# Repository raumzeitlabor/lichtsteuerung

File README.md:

RaumZeitLabor Lichtsteuerung
============================

https://wiki.raumzeitlabor.de/wiki/Lichtsteuerung

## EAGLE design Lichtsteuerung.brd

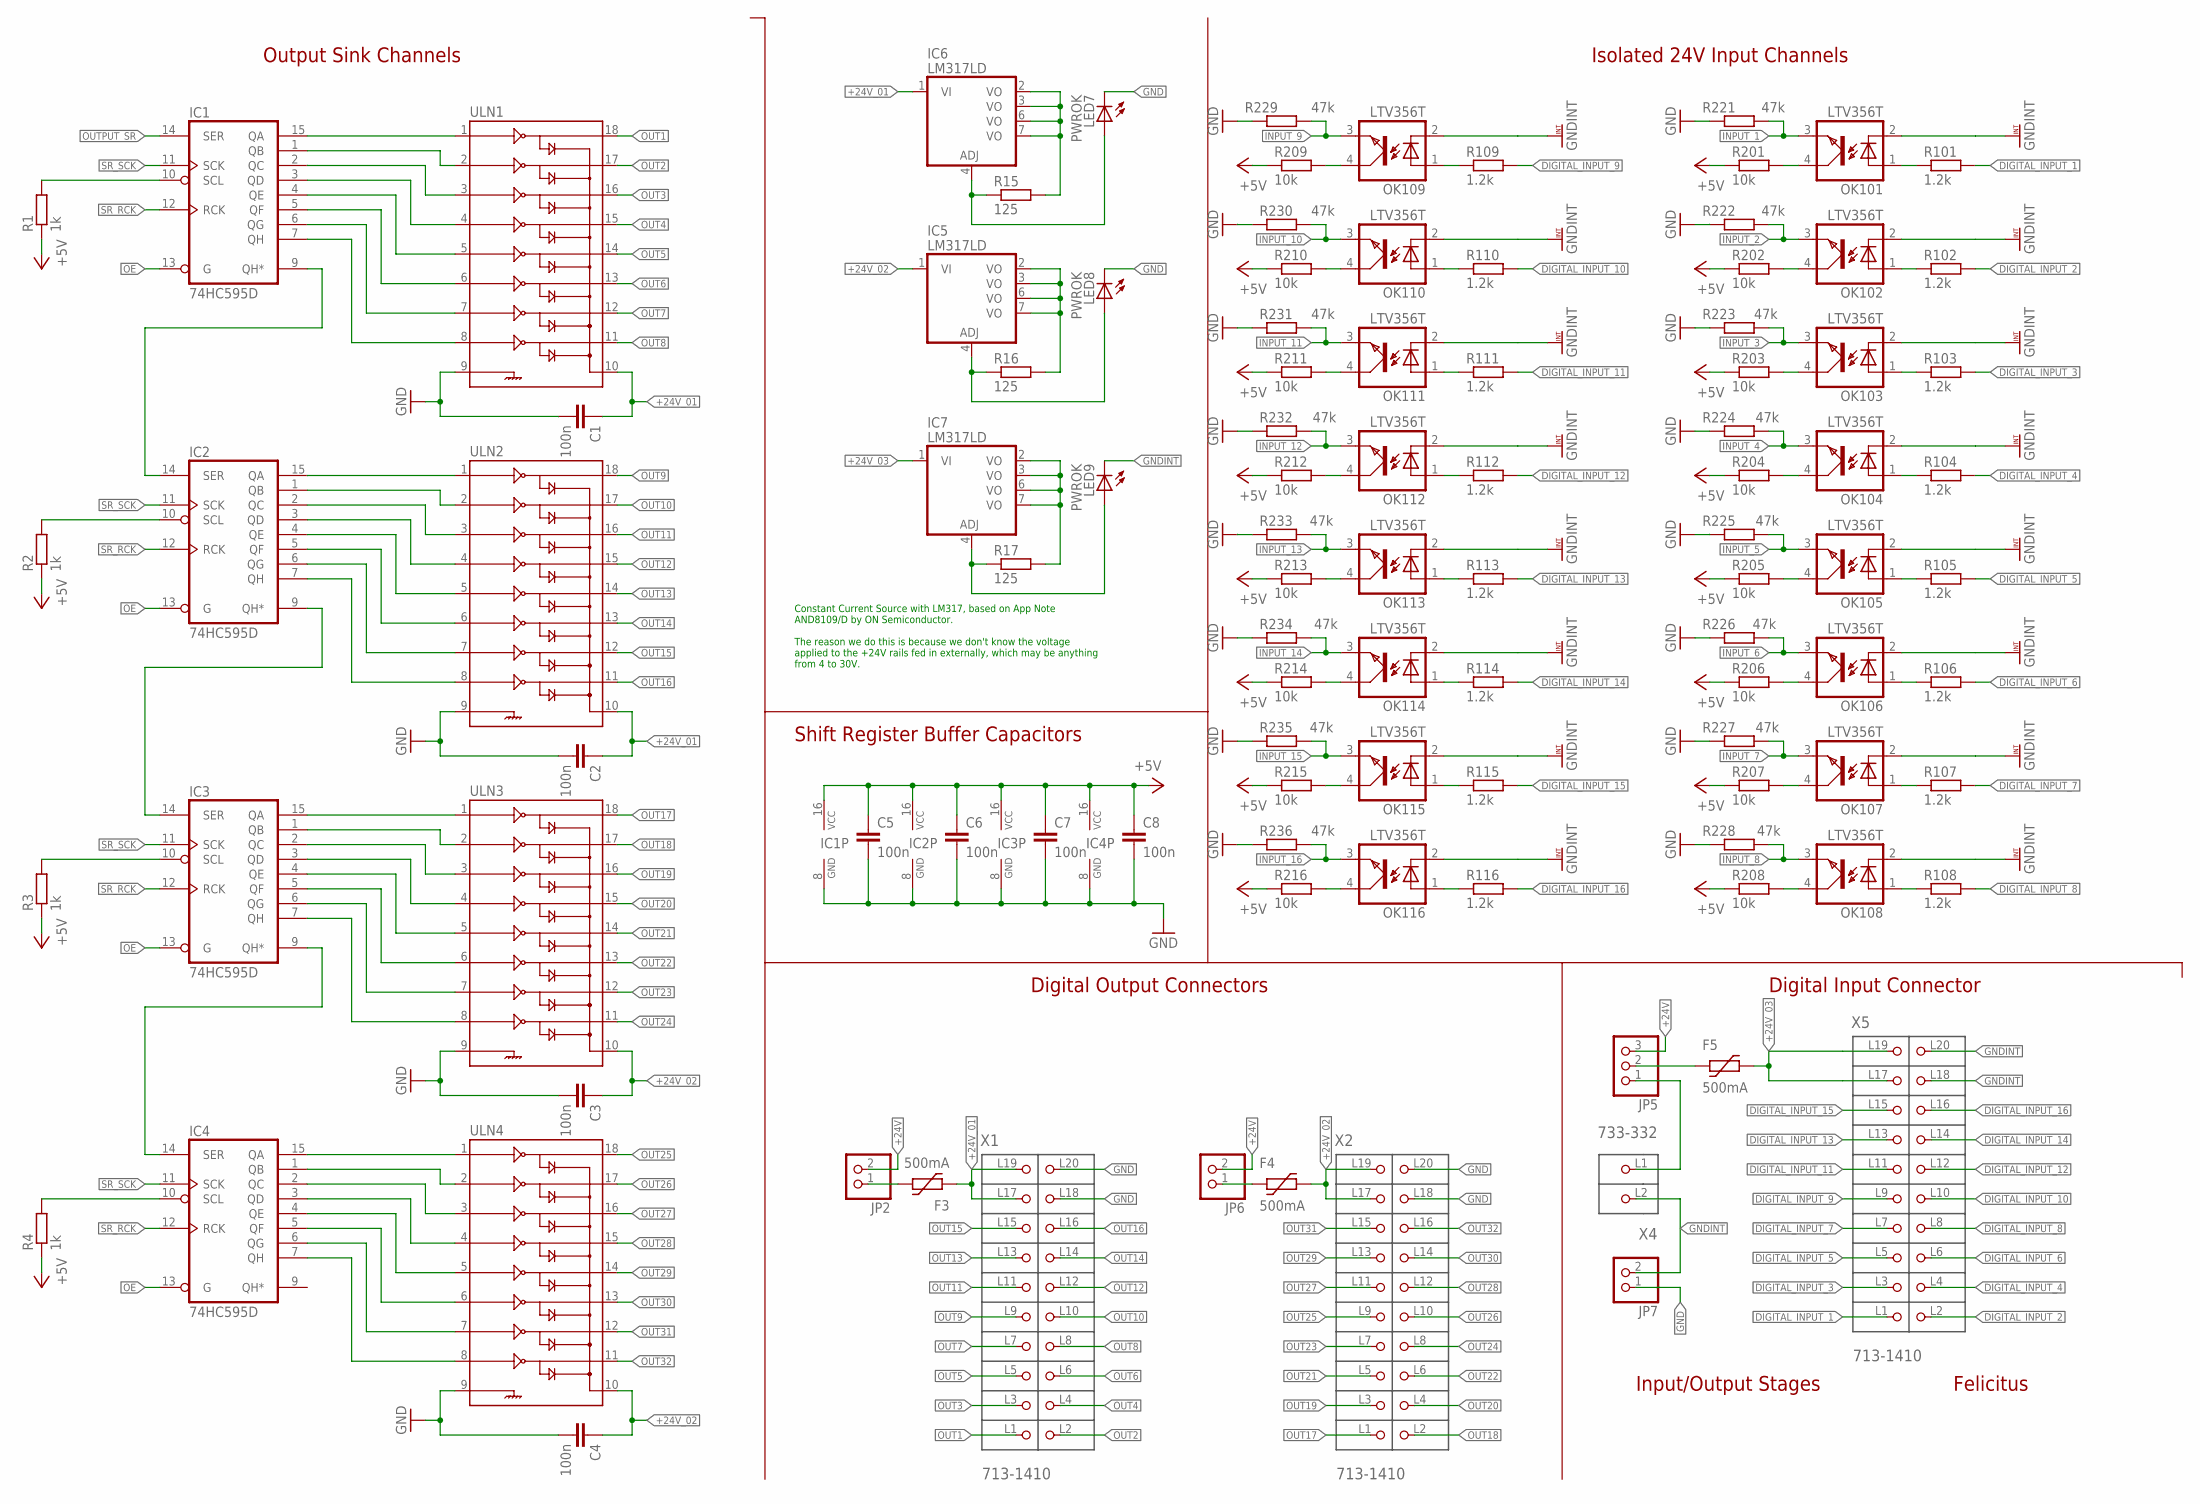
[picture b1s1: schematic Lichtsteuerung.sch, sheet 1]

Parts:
C1, C2, C3, C4, C5, C6, C7, C8: 100n; C0805
F3, F4, F5: 500mA; 1812L
IC1, IC2, IC3, IC4: 74HC595D; SO16
IC5, IC6, IC7: LM317LD; SO08
JP2, JP6, JP7: PINHD-1X2; 1X02
JP5: PINHD-1X3; 1X03
LED7, LED8, LED9: PWROK; CHIP-LED0805
OK101, OK102, OK103, OK104, OK105, OK106, OK107, OK108, OK109, OK110, OK111, OK112, OK113, OK114, OK115, OK116: LTV356T; SMD4
R1, R2, R3, R4: 1k; R0805
R15, R16, R17: 125; R0805
R101, R102, R103, R104, R105, R106, R107, R108, R109, R110, R111, R112, R113, R114, R115, R116: 1.2k; R0805
R201, R202, R203, R204, R205, R206, R207, R208, R209, R210, R211, R212, R213, R214, R215, R216: 10k; R0805
R221, R222, R223, R224, R225, R226, R227, R228, R229, R230, R231, R232, R233, R234, R235, R236: 47k; R0805
ULN1, ULN2, ULN3, ULN4: ULN2803SOICW; SO18L
X1, X2, X5: 713-1410; P-713-1410
X4: 733-332; P-733-332

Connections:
+5V: C5.1, C6.1, C7.1, C8.1, IC1.16 (VCC), IC2.16 (VCC), IC3.16 (VCC), IC4.16 (VCC), R1.1, R2.1, R3.1, R4.1, R201.1, R202.1, R203.1, R204.1, R205.1, R206.1, R207.1, R208.1, R209.1, R210.1, R211.1, R212.1, R213.1, R214.1, R215.1, R216.1; also elsewhere on the board
+24V: JP2.2, JP5.3, JP6.2; also elsewhere on the board
+24V_01: C1.1, C2.1, F3.P$1 (1), IC6.1 (VI), ULN1.10, ULN2.10, X1.L17, X1.L19
+24V_02: C3.1, C4.1, F4.P$2 (2), IC5.1 (VI), ULN3.10, ULN4.10, X2.L17, X2.L19
+24V_03: F5.P$2 (2), IC7.1 (VI), X5.L17, X5.L19
DIGITAL_INPUT_1: R101.2, X5.L1
DIGITAL_INPUT_2: R102.2, X5.L2
DIGITAL_INPUT_3: R103.2, X5.L3
DIGITAL_INPUT_4: R104.2, X5.L4
DIGITAL_INPUT_5: R105.2, X5.L5
DIGITAL_INPUT_6: R106.2, X5.L6
DIGITAL_INPUT_7: R107.2, X5.L7
DIGITAL_INPUT_8: R108.2, X5.L8
DIGITAL_INPUT_9: R109.2, X5.L9
DIGITAL_INPUT_10: R110.2, X5.L10
DIGITAL_INPUT_11: R111.2, X5.L11
DIGITAL_INPUT_12: R112.2, X5.L12
DIGITAL_INPUT_13: R113.2, X5.L13
DIGITAL_INPUT_14: R114.2, X5.L14
DIGITAL_INPUT_15: R115.2, X5.L15
DIGITAL_INPUT_16: R116.2, X5.L16
GND: C1.2, C2.2, C3.2, C4.2, C5.2, C6.2, C7.2, C8.2, IC1.8 (GND), IC2.8 (GND), IC3.8 (GND), IC4.8 (GND), JP7.1, LED7.C, LED8.C, R221.1, R222.1, R223.1, R224.1, R225.1, R226.1, R227.1, R228.1, R229.1, R230.1, R231.1, R232.1, R233.1, R234.1, R235.1, R236.1, ULN1.9, ULN2.9, ULN3.9, ULN4.9, X1.L18, X1.L20, X2.L18, X2.L20; also elsewhere on the board
GNDINT: JP7.2, LED9.C, OK101.2 (C), OK102.2 (C), OK103.2 (C), OK104.2 (C), OK105.2 (C), OK106.2 (C), OK107.2 (C), OK108.2 (C), OK109.2 (C), OK110.2 (C), OK111.2 (C), OK112.2 (C), OK113.2 (C), OK114.2 (C), OK115.2 (C), OK116.2 (C), X4.L2 (P2), X5.L18, X5.L20; also elsewhere on the board
INPUT_1: OK101.3 (EMIT), R221.2; also elsewhere on the board
INPUT_2: OK102.3 (EMIT), R222.2; also elsewhere on the board
INPUT_3: OK103.3 (EMIT), R223.2; also elsewhere on the board
INPUT_4: OK104.3 (EMIT), R224.2; also elsewhere on the board
INPUT_5: OK105.3 (EMIT), R225.2; also elsewhere on the board
INPUT_6: OK106.3 (EMIT), R226.2; also elsewhere on the board
INPUT_7: OK107.3 (EMIT), R227.2; also elsewhere on the board
INPUT_8: OK108.3 (EMIT), R228.2; also elsewhere on the board
INPUT_9: OK109.3 (EMIT), R229.2; also elsewhere on the board
INPUT_10: OK110.3 (EMIT), R230.2; also elsewhere on the board
INPUT_11: OK111.3 (EMIT), R231.2; also elsewhere on the board
INPUT_12: OK112.3 (EMIT), R232.2; also elsewhere on the board
INPUT_13: OK113.3 (EMIT), R233.2; also elsewhere on the board
INPUT_14: OK114.3 (EMIT), R234.2; also elsewhere on the board
INPUT_15: OK115.3 (EMIT), R235.2; also elsewhere on the board
INPUT_16: OK116.3 (EMIT), R236.2; also elsewhere on the board
unnamed: IC1.15 (QA), ULN1.1
unnamed: IC1.1 (QB), ULN1.2
unnamed: IC1.2 (QC), ULN1.3
unnamed: IC1.3 (QD), ULN1.4
unnamed: IC1.4 (QE), ULN1.5
unnamed: IC1.5 (QF), ULN1.6
unnamed: IC1.6 (QG), ULN1.7
unnamed: IC1.7 (QH), ULN1.8
unnamed: IC2.15 (QA), ULN2.1
unnamed: IC2.1 (QB), ULN2.2
unnamed: IC2.2 (QC), ULN2.3
unnamed: IC2.3 (QD), ULN2.4
unnamed: IC2.4 (QE), ULN2.5
unnamed: IC2.5 (QF), ULN2.6
unnamed: IC2.6 (QG), ULN2.7
unnamed: IC2.7 (QH), ULN2.8
unnamed: IC3.15 (QA), ULN3.1
unnamed: IC3.1 (QB), ULN3.2
unnamed: IC3.2 (QC), ULN3.3
unnamed: IC3.3 (QD), ULN3.4
unnamed: IC3.4 (QE), ULN3.5
unnamed: IC3.5 (QF), ULN3.6
unnamed: IC3.6 (QG), ULN3.7
unnamed: IC3.7 (QH), ULN3.8
unnamed: IC4.15 (QA), ULN4.1
unnamed: IC4.1 (QB), ULN4.2
unnamed: IC4.2 (QC), ULN4.3
unnamed: IC4.3 (QD), ULN4.4
unnamed: IC4.4 (QE), ULN4.5
unnamed: IC4.5 (QF), ULN4.6
unnamed: IC4.6 (QG), ULN4.7
unnamed: IC4.7 (QH), ULN4.8
unnamed: IC1.9 (QH*), IC2.14 (SER)
unnamed: IC2.9 (QH*), IC3.14 (SER)
unnamed: IC3.9 (QH*), IC4.14 (SER)
unnamed: IC1.10 (SCL), R1.2
unnamed: IC2.10 (SCL), R2.2
unnamed: IC3.10 (SCL), R3.2
unnamed: IC4.10 (SCL), R4.2
unnamed: F5.P$1 (1), JP5.2
unnamed: JP5.1, X4.L1 (P1)
unnamed: OK101.1 (A), R101.1
unnamed: OK101.4 (COL), R201.2
unnamed: OK102.1 (A), R102.1
unnamed: OK102.4 (COL), R202.2
unnamed: OK103.1 (A), R103.1
unnamed: OK103.4 (COL), R203.2
unnamed: OK104.1 (A), R104.1
unnamed: OK104.4 (COL), R204.2
unnamed: OK105.1 (A), R105.1
unnamed: OK105.4 (COL), R205.2
unnamed: OK106.1 (A), R106.1
unnamed: OK106.4 (COL), R206.2
unnamed: OK107.1 (A), R107.1
unnamed: OK107.4 (COL), R207.2
unnamed: OK108.1 (A), R108.1
unnamed: OK108.4 (COL), R208.2
unnamed: OK109.1 (A), R109.1
unnamed: OK109.4 (COL), R209.2
unnamed: OK110.1 (A), R110.1
unnamed: OK110.4 (COL), R210.2
unnamed: OK111.1 (A), R111.1
unnamed: F4.P$1 (1), JP6.1
unnamed: OK111.4 (COL), R211.2
unnamed: F3.P$2 (2), JP2.1
unnamed: OK112.1 (A), R112.1
unnamed: IC5.4 (ADJ), LED8.A, R16.1
unnamed: OK112.4 (COL), R212.2
unnamed: IC5.2 (VO), IC5.3 (VO), IC5.6 (VO), IC5.7 (VO), R16.2
unnamed: IC7.4 (ADJ), LED9.A, R17.1
unnamed: OK113.1 (A), R113.1
unnamed: IC6.4 (ADJ), LED7.A, R15.1
unnamed: IC6.2 (VO), IC6.3 (VO), IC6.6 (VO), IC6.7 (VO), R15.2
unnamed: OK113.4 (COL), R213.2
unnamed: IC7.2 (VO), IC7.3 (VO), IC7.6 (VO), IC7.7 (VO), R17.2
unnamed: OK114.1 (A), R114.1
unnamed: OK114.4 (COL), R214.2
unnamed: OK115.1 (A), R115.1
unnamed: OK115.4 (COL), R215.2
unnamed: OK116.1 (A), R116.1
unnamed: OK116.4 (COL), R216.2
OE: IC1.13 (G), IC2.13 (G), IC3.13 (G), IC4.13 (G); also elsewhere on the board
OUT1: ULN1.18, X1.L1
OUT2: ULN1.17, X1.L2
OUT3: ULN1.16, X1.L3
OUT4: ULN1.15, X1.L4
OUT5: ULN1.14, X1.L5
OUT6: ULN1.13, X1.L6
OUT7: ULN1.12, X1.L7
OUT8: ULN1.11, X1.L8
OUT9: ULN2.18, X1.L9
OUT10: ULN2.17, X1.L10
OUT11: ULN2.16, X1.L11
OUT12: ULN2.15, X1.L12
OUT13: ULN2.14, X1.L13
OUT14: ULN2.13, X1.L14
OUT15: ULN2.12, X1.L15
OUT16: ULN2.11, X1.L16
OUT17: ULN3.18, X2.L1
OUT18: ULN3.17, X2.L2
OUT19: ULN3.16, X2.L3
OUT20: ULN3.15, X2.L4
OUT21: ULN3.14, X2.L5
OUT22: ULN3.13, X2.L6
OUT23: ULN3.12, X2.L7
OUT24: ULN3.11, X2.L8
OUT25: ULN4.18, X2.L9
OUT26: ULN4.17, X2.L10
OUT27: ULN4.16, X2.L11
OUT28: ULN4.15, X2.L12
OUT29: ULN4.14, X2.L13
OUT30: ULN4.13, X2.L14
OUT31: ULN4.12, X2.L15
OUT32: ULN4.11, X2.L16
OUTPUT_SR: IC1.14 (SER); also elsewhere on the board
SR_RCK: IC1.12 (RCK), IC2.12 (RCK), IC3.12 (RCK), IC4.12 (RCK); also elsewhere on the board
SR_SCK: IC1.11 (SCK), IC2.11 (SCK), IC3.11 (SCK), IC4.11 (SCK); also elsewhere on the board

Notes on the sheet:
Felicitus
Output Sink Channels
Shift Register Buffer Capacitors
Input/Output Stages
Isolated 24V Input Channels
Digital Input Connector
Digital Output Connectors
Constant Current Source with LM317, based on App Note AND8109/D by ON Semiconductor. The reason we do this is because we don't know the voltage applied to the +24V rails fed in externally, which may be anything from 4 to 30V.

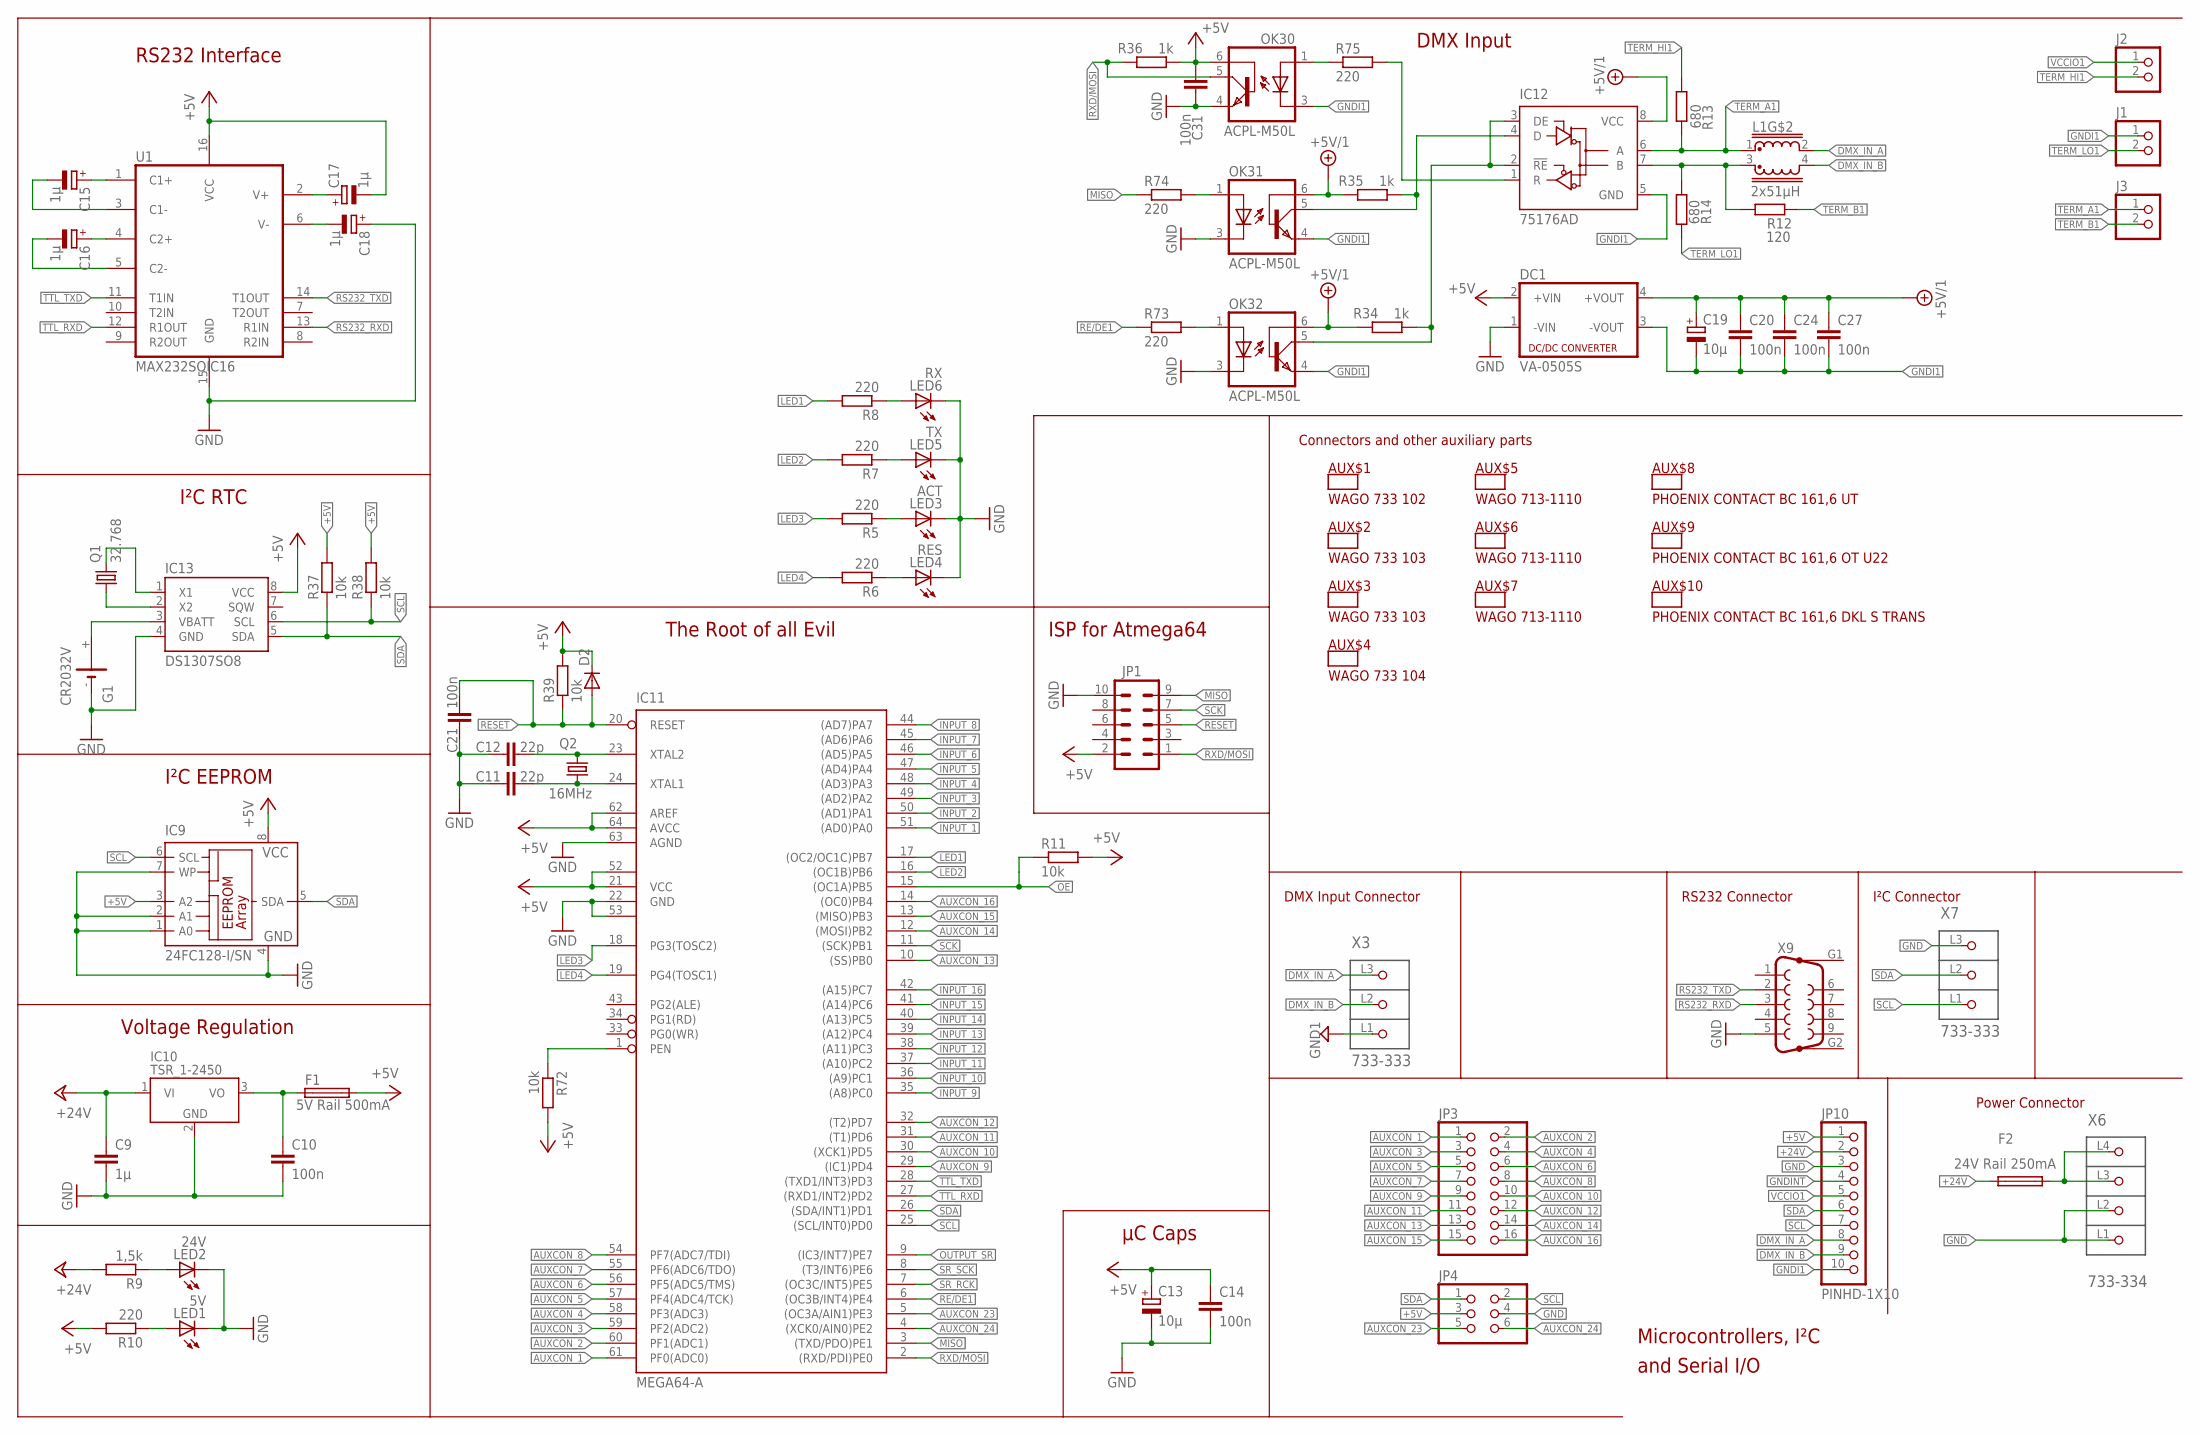
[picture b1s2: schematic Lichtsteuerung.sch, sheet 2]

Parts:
C9: 1µ; C0805
C10, C14, C20, C21, C24, C27, C31: 100n; C0805
C11, C12: 22p; C0805
C13, C19: 10µ; C/6032-28R; PARTKEEPR_SKU 2607
C15, C16, C17, C18: 1µ; A/3216-18R; PARTKEEPR_SKU 2609
D2: DIODE-SOD323-R; SOD323-R
DC1: VA-0505S; 4SIL
F1: 5V Rail 500mA; OMNIBLOK
F2: 24V Rail 250mA; OMNIBLOK
G1: CR2032V; CR2032V2
IC9: 24FC128-I/SN; SO-08M
IC10: TSR_1-2450; TSR-1
IC11: MEGA64-A; TQFP64
IC12: 75176AD; D_R-PDSO-G8
IC13: DS1307SO8; SO08
J1, J2, J3: PINHD-1X2; 1X02
JP1: ML10
JP3: PINHD-2X8; 2X08
JP4: PINHD-2X3; 2X03
JP10: PINHD-1X10; 1X10-BIG
L1: 2x51µH; EPCOS_B82790_SERIES
LED1: 5V; CHIP-LED0805
LED2: 24V; CHIP-LED0805
LED3: ACT; CHIP-LED0805
LED4: RES; CHIP-LED0805
LED5: TX; CHIP-LED0805
LED6: RX; CHIP-LED0805
OK30, OK31, OK32: ACPL-M50L; JEDEC_MS-012-AA_SOIC5
Q1: 32.768; MC-306
Q2: 16MHz; MJ
R5, R6, R7, R8, R10, R73, R74, R75: 220; R0805
R9: 1,5k; R0805
R11, R37, R38, R39, R72: 10k; R0805
R12: 120; R0805
R13, R14: 680; R0805
R34, R35, R36: 1k; R0805
U1: MAX232SOIC16; SO016
X3, X7: 733-333; P-733-333
X6: 733-334; P-733-334
X9: F09VP

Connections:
+5V: C13.+, C14.1, C17.-, C31.1, D2.C, DC1.2 (+VIN), F1.P$2 (2), IC9.3 (A2), IC9.8 (VCC), IC11.21 (VCC), IC11.52 (VCC1), IC11.62 (AREF), IC11.64 (AVCC), IC13.8 (VCC), JP1.2, JP4.3, JP10.1, OK30.6 (BAS), R10.2, R11.2, R36.1, R37.2, R38.2, R39.2, R72.2, U1.16 (VCC); also elsewhere on the board
+24V: C9.1, F2.P$1 (1), IC10.1 (VI), JP10.2, R9.2; also elsewhere on the board
+24VIN: F2.P$2 (2), X6.L3 (P3), X6.L4 (P4)
AUXCON_1: IC11.61 (PF0(ADC0)), JP3.1
AUXCON_2: IC11.60 (PF1(ADC1)), JP3.2
AUXCON_3: IC11.59 (PF2(ADC2)), JP3.3
AUXCON_4: IC11.58 (PF3(ADC3)), JP3.4
AUXCON_5: IC11.57 (PF4(ADC4/TCK)), JP3.5
AUXCON_6: IC11.56 (PF5(ADC5/TMS)), JP3.6
AUXCON_7: IC11.55 (PF6(ADC6/TDO)), JP3.7
AUXCON_8: IC11.54 (PF7(ADC7/TDI)), JP3.8
AUXCON_9: IC11.29 ((IC1)PD4), JP3.9
AUXCON_10: IC11.30 ((XCK1)PD5), JP3.10
AUXCON_11: IC11.31 ((T1)PD6), JP3.11
AUXCON_12: IC11.32 ((T2)PD7), JP3.12
AUXCON_13: IC11.10 ((SS)PB0), JP3.13
AUXCON_14: IC11.12 ((MOSI)PB2), JP3.14
AUXCON_15: IC11.13 ((MISO)PB3), JP3.15
AUXCON_16: IC11.14 ((OC0)PB4), JP3.16
AUXCON_23: IC11.5 ((OC3A/AIN1)PE3), JP4.5
AUXCON_24: IC11.4 ((XCK0/AIN0)PE2), JP4.6
DMX_IN_A: JP10.8, L1.2 (4), X3.L3 (P3)
DMX_IN_B: JP10.9, L1.4, X3.L2 (P2)
GND: C9.2, C10.2, C11.2, C12.2, C13.-, C14.2, C18.+, C21.2, C31.2, DC1.1 (-VIN), G1.-, IC9.1 (A0), IC9.2 (A1), IC9.4 (GND), IC9.7 (WP), IC10.2 (GND), IC11.22 (GND), IC11.53 (GND1), IC11.63 (AGND), IC13.4 (GND), JP1.10, JP4.4, JP10.3, LED1.C, LED2.C, LED3.C, LED4.C, LED5.C, LED6.C, OK30.4 (EMI), OK31.3 (C), OK32.3 (C), U1.15 (GND), X6.L1 (P1), X6.L2 (P2), X7.L3 (P3), X9.5; also elsewhere on the board
GNDI1: C19.-, C20.2, C24.2, C27.2, DC1.3 (-VOUT), IC12.5 (GND), J1.1, JP10.10, OK30.3 (C), OK31.4 (EMI), OK32.4 (EMI), X3.L1 (P1)
GNDINT: JP10.4; also elsewhere on the board
INPUT_1: IC11.51 ((AD0)PA0); also elsewhere on the board
INPUT_2: IC11.50 ((AD1)PA1); also elsewhere on the board
INPUT_3: IC11.49 ((AD2)PA2); also elsewhere on the board
INPUT_4: IC11.48 ((AD3)PA3); also elsewhere on the board
INPUT_5: IC11.47 ((AD4)PA4); also elsewhere on the board
INPUT_6: IC11.46 ((AD5)PA5); also elsewhere on the board
INPUT_7: IC11.45 ((AD6)PA6); also elsewhere on the board
INPUT_8: IC11.44 ((AD7)PA7); also elsewhere on the board
INPUT_9: IC11.35 ((A8)PC0); also elsewhere on the board
INPUT_10: IC11.36 ((A9)PC1); also elsewhere on the board
INPUT_11: IC11.37 ((A10)PC2); also elsewhere on the board
INPUT_12: IC11.38 ((A11)PC3); also elsewhere on the board
INPUT_13: IC11.39 ((A12)PC4); also elsewhere on the board
INPUT_14: IC11.40 ((A13)PC5); also elsewhere on the board
INPUT_15: IC11.41 ((A14)PC6); also elsewhere on the board
INPUT_16: IC11.42 ((A15)PC7); also elsewhere on the board
LED1: IC11.17 ((OC2/OC1C)PB7), R8.2
LED2: IC11.16 ((OC1B)PB6), R7.2
LED3: IC11.18 (PG3(TOSC2)), R5.2
LED4: IC11.19 (PG4(TOSC1)), R6.2
MISO: IC11.3 ((TXD/PDO)PE1), JP1.9, R74.1
unnamed: G1.+, IC13.3 (VBATT)
unnamed: C11.1, IC11.24 (XTAL1), Q2.P3 (2)
unnamed: IC13.2 (X2), Q1.1
unnamed: IC13.1 (X1), Q1.4 (2)
unnamed: C12.1, IC11.23 (XTAL2), Q2.P1 (1)
unnamed: LED6.A, R8.1
unnamed: LED5.A, R7.1
unnamed: LED3.A, R5.1
unnamed: C15.+, U1.1 (C1+)
unnamed: C15.-, U1.3 (C1-)
unnamed: LED4.A, R6.1
unnamed: LED1.A, R10.1
unnamed: LED2.A, R9.1
unnamed: IC11.1 (PEN), R72.1
unnamed: C16.+, U1.4 (C2+)
unnamed: C16.-, U1.5 (C2-)
unnamed: C10.1, F1.P$1 (1), IC10.3 (VO)
unnamed: IC12.7 (B), L1.3 (1), R12.2, R14.2
unnamed: OK30.1 (A), R75.1
unnamed: OK31.1 (A), R74.2
unnamed: OK32.1 (A), R73.2
unnamed: C18.-, U1.6 (V-)
unnamed: C17.+, U1.2 (V+)
OE: IC11.15 ((OC1A)PB5), R11.1; also elsewhere on the board
OUTPUT_SR: IC11.9 ((IC3/INT7)PE7); also elsewhere on the board
RE/DE1: IC11.6 ((OC3B/INT4)PE4), R73.1
REC$1: IC12.1 (R), R75.2
RESET: C21.1, D2.A, IC11.20 (RESET), JP1.5, R39.1
RE_OUT: IC12.2 (!RE), IC12.3 (DE), OK32.5 (COL), R34.1
RS232_RXD: U1.13 (R1IN), X9.3
RS232_TXD: U1.14 (T1OUT), X9.2
RXD/MOSI: IC11.2 ((RXD/PDI)PE0), JP1.1, OK30.5 (COL), R36.2
SCK: IC11.11 ((SCK)PB1), JP1.7
SCL: IC9.6 (SCL), IC11.25 ((SCL/INT0)PD0), IC13.6 (SCL), JP4.2, JP10.7, R38.1, X7.L1 (P1)
SDA: IC9.5 (SDA), IC11.26 ((SDA/INT1)PD1), IC13.5 (SDA), JP4.1, JP10.6, R37.1, X7.L2 (P2)
SR_RCK: IC11.7 ((OC3C/INT5)PE5); also elsewhere on the board
SR_SCK: IC11.8 ((T3/INT6)PE6); also elsewhere on the board
TERM_A1: IC12.6 (A), J3.1, L1.1, R13.1
TERM_B1: J3.2, R12.1
TERM_HI1: J2.2, R13.2
TERM_LO1: J1.2, R14.1
TTL_RXD: IC11.27 ((RXD1/INT2)PD2), U1.12 (R1OUT)
TTL_TXD: IC11.28 ((TXD1/INT3)PD3), U1.11 (T1IN)
TXD_OUT: IC12.4 (D), OK31.5 (COL), R35.1
VCCIO1: C19.+, C20.1, C24.1, C27.1, DC1.4 (+VOUT), IC12.8 (VCC), J2.1, JP10.5, OK31.6 (BAS), OK32.6 (BAS), R34.2, R35.2

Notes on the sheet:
I²C EEPROM
I²C RTC
Voltage Regulation
DMX Input
ISP for Atmega64
µC Caps
RS232 Interface
The Root of all Evil
Microcontrollers, I²C
and Serial I/O
DMX Input Connector
RS232 Connector
I²C Connector
Power Connector
Connectors and other auxiliary parts

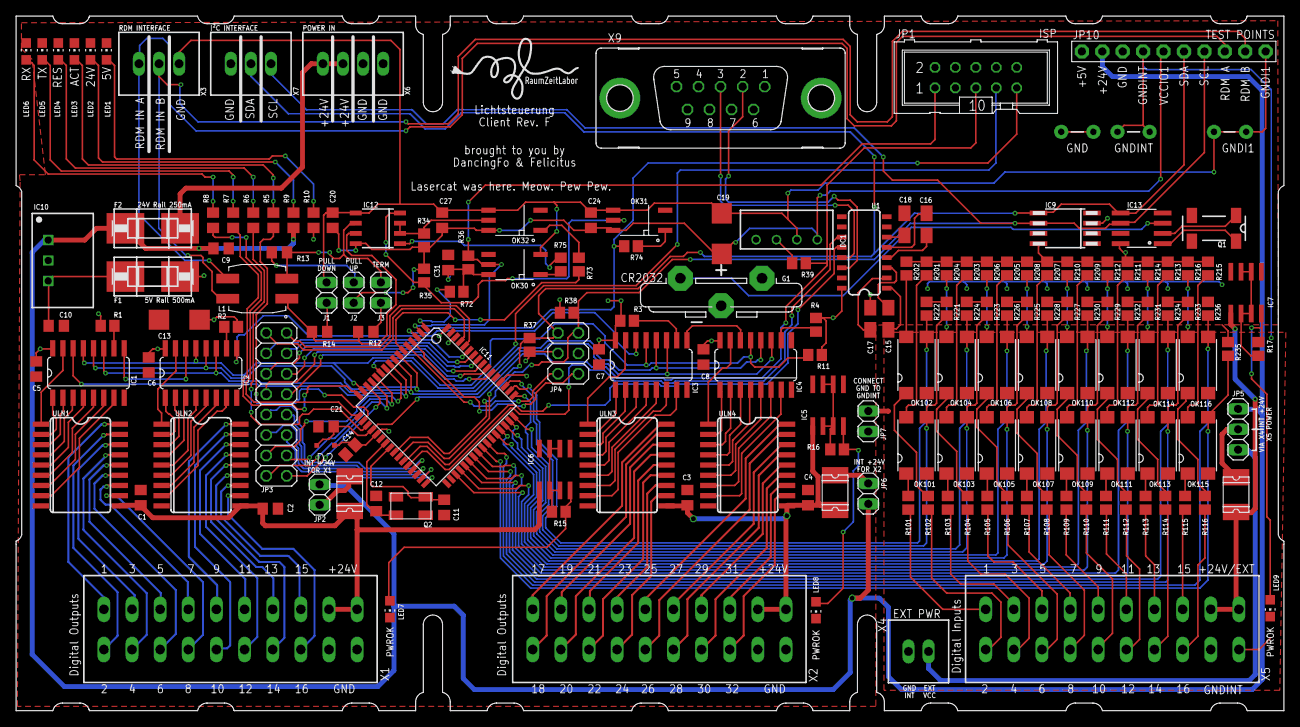
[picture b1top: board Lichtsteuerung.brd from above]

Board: 2 copper layers, 157.7 x 86.4 mm, 175 parts (0 on the bottom side), 224 nets.

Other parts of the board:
U$1: RAUMZEITLABOR_FILLED_16MM

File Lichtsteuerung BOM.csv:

Qty	Value	Device	Package	Parts	Description	MF	MPN	OC_FARNELL	OC_NEWARK	OC_REICHELT	EP	GP
1		F09VP	F09VP	X9	SUB-D			unknown	unknown	D-SUB BU 09TL	1,95	1,95
1		PINHD-2X8	2X08	JP3	PIN HEADER					SL 2X10G 2,54	0,07	0,07
4		ULN2803SOICW	SO18L	ULN1, ULN2, ULN3, ULN4	Darlington Driver					ULN 2803 D	0,42	1,68
16	1.2k	R-EU_R0805	R0805	R101, R102, R103, R104, R105, R106, R107, R108, R109, R110, R111, R112, R113, R114, R115, R116	RESISTOR, European symbol					SMD-0805 1,20K	0,025	0,4
3	100n	C-EUC0805	C0805	C10, C20, C23	CAPACITOR, European symbol					X7R-G0805 100N	0,05	0,15
8	100n	C-EUC0805	C0805	C1, C2, C3, C4, C5, C6, C7, C8	CAPACITOR, European symbol					X7R-G0805 100N	0,05	0,4
1	100n	C-EUC0805	C0805@1	C14	CAPACITOR, European symbol					X7R-G0805 100N	0,05	0,05
23	10k	R-EU_R0805	R0805	R8, R37, R38, R39, R40, R72, R76, R201, R202, R203, R204, R205, R206, R207, R208, R209, R210, R211, R212, R213, R214, R215, R216	RESISTOR, European symbol					SMD-0805 10,0K	0,025	0,575
1	125mA	SMD-MICRO-FUSE-BLOCK	OMNIBLOK	F2						SMD-HASF 0,25A	1,1	1,1
2	16MHz	CRYSTALCTS406	CTS406	Q2, Q3	CRYSTAL			unknown	unknown	16,000000-MQ	0,75	1,5
4	1k	R-EU_R0805	R0805	R1, R2, R3, R4	RESISTOR, European symbol					SMD-0805 1,00K	0,025	0,1
4	1µ	CPOL-EU153CLV-0405	153CLV-0405	C15, C16, C17, C18	POLARIZED CAPACITOR, European symbol					VF 1,0/50 C-B	0,15	0,6
6	220	R-EU_R0805	R0805	R5, R6, R7, R73, R74, R75	RESISTOR, European symbol					SMD-0805 220	0,025	0,15
1	220µ	CPOL-EU150CLZ-1010	150CLZ-1010	C13	POLARIZED CAPACITOR, European symbol					VF 220/6,3 K-D	0,14	0,14
2	220µ	CPOL-EUD	PANASONIC_D	C19, C22	POLARIZED CAPACITOR, European symbol					VF 220/6,3 K-D	0,14	0,28
4	22p	C-EUC0805	C0805	C11, C12, C25, C26	CAPACITOR, European symbol					NPO-G0805 22P	0,05	0,2
1	24FC128-I/SN	24AA256SN	SO-08	IC9	Serial EEPROM		24AA256T-I/SM	1579570	08N6838	24AA1025-I/SM	3,5	3,5
2	2x51µH	EPCOS_B82790C0	EPCOS_B82790_SERIES	L1, L2	EPCOS B82790C0 Data and Signal Line Common Mode Choke					CONRAD		0
1	32768	MC-406	MC-406	Q1	kHz RANGE CRYSTAL UNIT SMD	BANNER ENGINEERING CORPORATION	MQDMC-406	1216226	21H2317	0,032768-SMD	0,35	0,35
1	330n	C-EUC0805	C0805	C9	CAPACITOR, European symbol					X7R-G0805 1,0/50	0,07	0,07
1	500mA	SMD-MICRO-FUSE-BLOCK	OMNIBLOK	F1						SMD-HASF 0,5A	1,15	1,15
3	713-1410	713-1410	P-713-1410	X1, X2, X5						WAGO 713-1410	3,3	9,9
1	733-332	733-332	P-733-332	X7						WAGO 733-332	0,46	0,46
2	733-333	733-333	P-733-333	X3, X8						WAGO 733-333	0,64	1,28
1	733-334	733-334	P-733-334	X6						WAGO 733-334	0,86	0,86
3	713-1110	713-1110								WAGO 713-1110	9,5	28,5
1	733-102									WAGO 733-102	1,2	1,2
2	733-103									WAGO 733-103	1,55	3,1
1	733-104									WAGO 733-104	1,8	1,8
4	74HC595D	74HC595D	SO16	IC1, IC2, IC3, IC4	8-bit SHIFT REGISTER, output latch					SMD HC 595	0,22	0,88
2	75176AD	75176AD	D_R-PDSO-G8	IC5, IC12	DIFFERENTIAL BUS TRANSCEIVER					SN 75176BD	0,36	0,72
1	CR2032H	CR2032H	CR2032H	G1	LI BATTERY Varta					KZH 20-1	0,54	0,54
1	DS1307SO8	DS1307SO8	SO08	IC13						DS 1307Z	1,8	1,8
22	LTV356T	LTV816S	SMD4	OK17, OK18, OK19, OK20, OK21, OK22, OK101, OK102, OK103, OK104, OK105, OK106, OK107, OK108, OK109, OK110, OK111, OK112, OK113, OK114, OK115, OK116	OPTO COUPLER			unknown	unknown	LTV 356T-SMD	0,27	5,94
2	M05X2SHD_SMD	M05X2SHD_SMD	2X5-SHROUDED_SMD	JP1, JP2	Header 5x2					WSL 10G	0,08	0,16
1	MAX232SOIC16	MAX232SOIC16	SO016	U1	RS232 Transceiver					MAX 232 CSE SMD	0,74	0,74
1	MEGA64-A	MEGA64-A	TQFP64	IC11	MICROCONTROLLER					ATMEGA 64-16 TQ	7,25	7,25
1	MEGA8-AI	MEGA8-AI	TQFP32-08	IC6	MICROCONTROLLER		ATMEGA8-16AU	9171371	73M8863	ATMEGA 8A-AU	1,95	1,95
1	TSR_1-2450	TSR_1-2450	TSR-1	IC10	TRACO TSR-1 Series					TSR 1-2450	8,3	8,3
2	VA-0505S	VA-0505S	4SIL	DC1, DC2	DC DC Converter Single Output, 1 Watt			unknown	unknown	SIM1-0505 SIL4	3,25	6,5
												
												96,295

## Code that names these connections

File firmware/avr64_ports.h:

#include <avr/io.h>

#ifndef PORTS_H
#define	PORTS_H

// Main Shift Register Output
#define SR_OUTPUT_PIN PE7
#define SR_OUTPUT_PORT PORTE
#define SR_OUTPUT_DPORT DDRE

// Shift Register clock
#define SR_SCK_PIN PE6
#define SR_SCK_PORT PORTE
#define SR_SCK_DPORT DDRE

// Shift Register RCK
#define SR_RCK_PIN PE5
#define SR_RCK_PORT PORTE
#define SR_RCK_DPORT DDRE

#endif	/* PORTS_H */

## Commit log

2013-02-11 Alles, was ich von Felicitus bekommen habe
2013-04-01 Konvertierung zu Eagle6, 2 Common Mode Chokes für DMX-IO Filterung hinzugefügt
2013-04-25 Platine geroutet.
2013-04-29 Added BOM, updated parts
2013-04-29 Added pin descriptions to board, easter egg.
2013-04-30 RZL-Logo muss sein.
2013-05-03 Removed old board/schematic
2013-05-03 Added the panel SVG
2013-05-03 Added ventilation
2013-05-11 Added polyfuses for the 24V rails
2013-05-14 Fixed wrong battery holder
2013-05-14 Added missing bypass cap for the second avr
2013-05-14 Fixed serial eeprom footprint
2013-05-15 Fixed typo
2013-05-15 Added another aux connector to supply SDA, SCL, +5V and GND
2013-05-20 - Added GND for I²C connector - Added LEDs for power indication - Added output enable for shift registers - Moved pin headers to make room for cable - Added pullup/pulldown resistors and SMD jumpers 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
2013-05-20 Swapped RXD and TXD, because this is a DCE, not a DTE. In plain words: You can simply connect any USB-RS232 connector to the port now, instead of using a null modem cable with crossed RXD/TXD pairs.
2013-05-24 Changed CR2032 battery holder with a vertical one to allow easier replacements
2013-05-25 Added initial firmware stuff. This is an attempt to include bitlash from the beginning to have scripting functionality, but I'm not sure if it works out. The code is probably a bit messy; will be cle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
2013-06-04 Added missing pulldowns for the optocoupler inputs
2013-07-12 Added new high-speed optocouplers
2013-08-12 Re-added smd jumpers, fixed silkscreens and added a few test points
2013-08-12 Added reichelt ordercodes
2013-08-12 Fake commit to test the board gen hook
2013-08-12 Another hook test
2013-08-12 Final hook test, seems to work
2013-08-20 Fixed ACPL-M50L footprint size
2013-10-02 Removed old firmware stuff
2013-10-02 Added initial arduino firmware.
2013-10-02 Added readme for the firmware
2013-10-06 Changed pulldown resistors from 10k to 47k for the input optocouplers
2013-10-09 Replaced atmega8 with atmega168 in order to use the DMXSerial library
2013-10-09 Added experimental external power input, needs review from DaFo
2013-12-02 New test firmware
2013-12-02 Added instructions and makefile
2013-12-02 Updated docs
2013-12-05 Implemented setDeviceName and getDeviceName
2013-12-05 Fixed doc for setOutputState
2013-12-14 Initial revision F
    Changes:
    * Removed Atmega8 + second RS485 interface, because we're using an RS485 hub and RDM instead
    * Added more (software controlled) status LEDs
    * Added optional external VCC for the relais drivers
    * Replaced SMD solder jumpers with real jumpers for DMX Term / Pull Up / Pull Down
    * All components placed now on the first layer, in order to allow reflowing of the components
2013-12-14 Finalized Revision F
2013-12-14 Moved stuff from tValues to tNames layer
2013-12-14 Added missing designator for C4
2013-12-14 Additions: - Added POWER OK LEDs for the inputs/outputs with constant current source (in case we need to connect other voltages and a fixed resistors won't help) - Added test points for all major sig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
2013-12-14 - Moved POWEROK to the tNames layer and adjusted their size
2013-12-14 Implemented getDMXStartAddress, getRDMUID, setOutputName, getOutputName, setOutputState, getOutputState, toggleOutputState, setInputName and getInputName.
    getInputName, setInputName, getOutputName and setOutputName are not functional yet, because I can't test if the I²C EEPROM is working due to a wiring error.
2014-01-13 - Added some more missing functions (anyoutputon, listoutputs, setinputmode, getinputmode) - Added responder for message E120_DEFAULT_SLOT_VALUE - Block DMX input if DMX input differs from internal s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
2014-02-01 Added stub for E120_SLOT_DESCRIPTION
2014-02-02 Send 255 instead of 1 when a channel is turned on
2014-02-05 Make it RDM conform
2014-02-10 Fixed overlap
2014-02-12 Implemented listInputs, setInputMode, getInputMode, setInputName, setOutputName, getOutputName, setOutputName
2014-02-12 Return the slot name via RDM using slot_description
2014-02-12 Implemented the private flag for outputs, not yet transmitted via RDM
2014-02-12 Send private output information via RDM
2014-02-13 Added OLA RDMprotos
2014-02-21 Updated part ordering numbers, added connector plugs and case to the BOM
2014-08-16 Added instructions for installing arduino 1.5 on wheezy/jessie
2014-08-16 Converted to atmega2561, made bitlash running, externalized RDM stuff
2015-01-31 Added event handlers onInputN, onInputNOff and onInputNOn
2015-02-03 Added i²c eeprom backup/restore
2015-06-15 Readded onInputN handler
2015-09-19 Fixed length for ON/OFF strings
2015-09-19 Fixed LM317 to use constant current mode
2015-09-20 Added function to peep the external eeprom, added null character for buffers in listoutputs/listinputs
2015-09-20 Added function to peep the external eeprom
2015-09-20 Rewritten hex dump
2015-10-18 remove dmx dependency
2015-10-18 act as i2c device on address 0x23
2015-10-18 Switch to arduino-mk build
2016-08-28 Added TVS Diode and 100n capacitor for the reset line
